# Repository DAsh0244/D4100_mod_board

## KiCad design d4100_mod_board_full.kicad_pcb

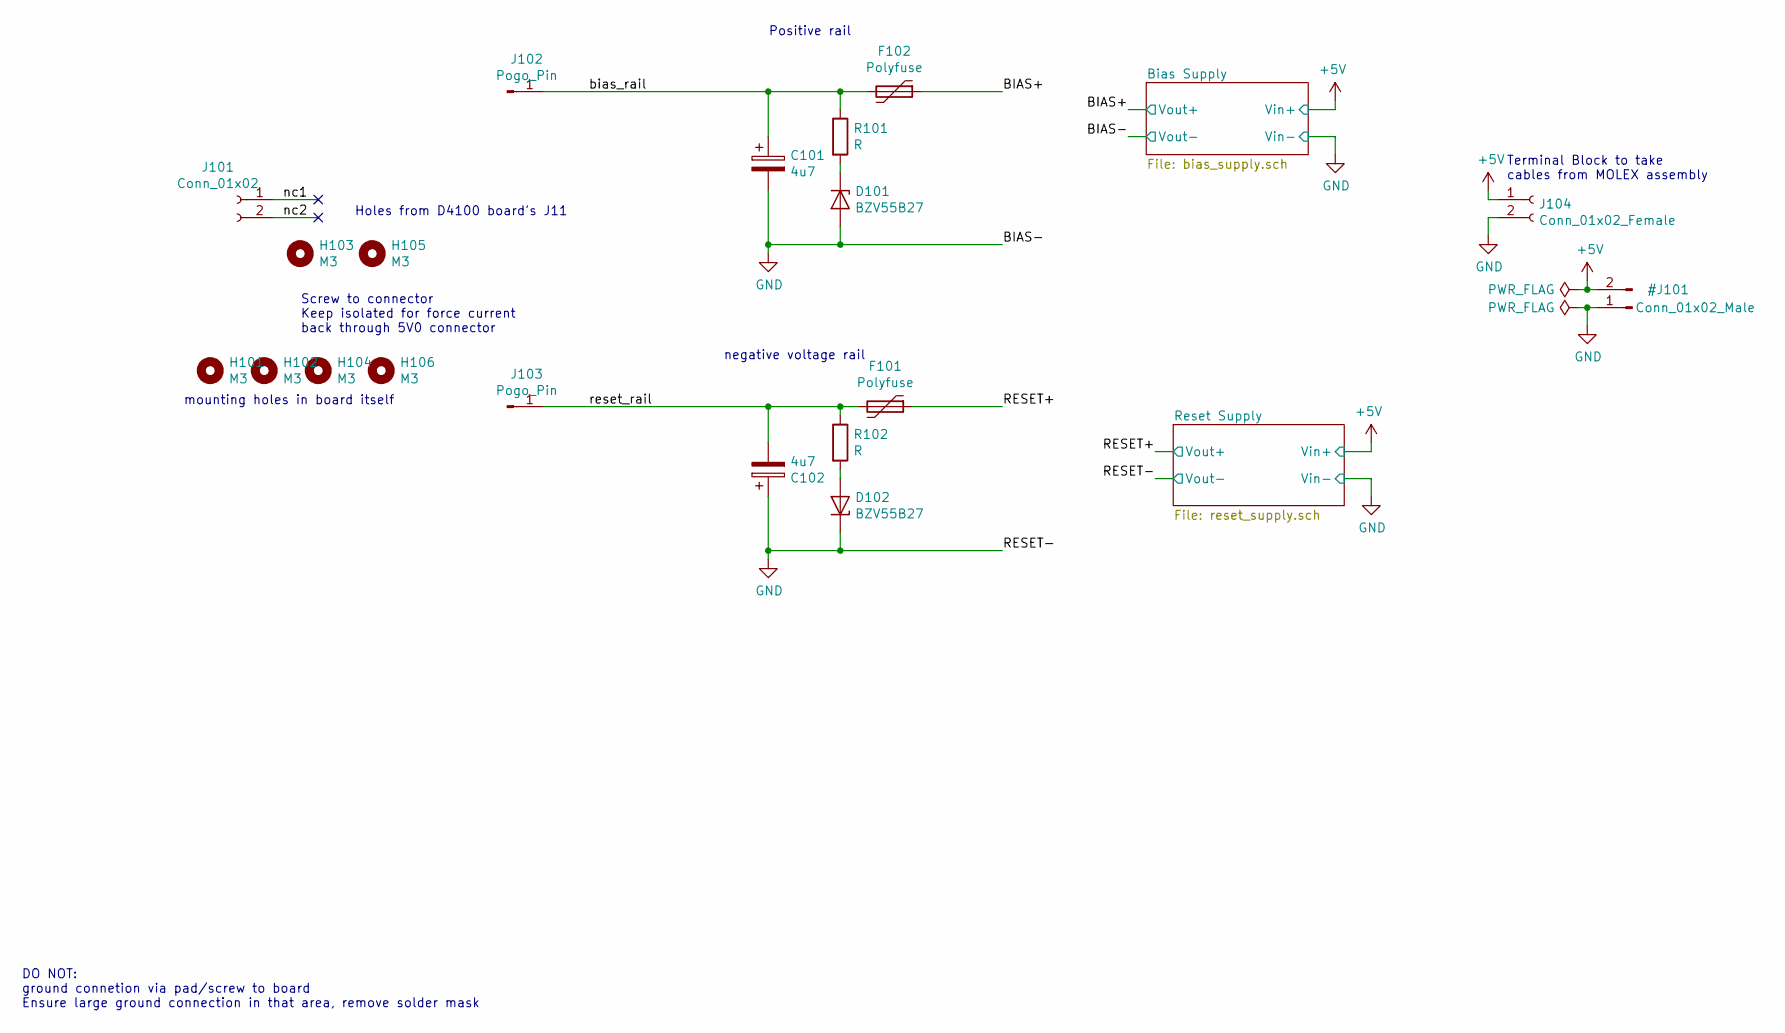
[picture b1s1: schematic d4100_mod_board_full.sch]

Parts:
C101, C102: 4u7; CP_Tantalum_Case-C_EIA-6032-28_Reflow
D101, D102: BZV55B27; D_MiniMELF
F101, F102: Polyfuse; Fuse_SMD1206_HandSoldering
H101, H102, H103, H104, H105, H106: M3; MountingHole_3.2mm_M3
J101: Conn_01x02; Pin_Header_Straight_1x02_Pitch2.54mm
J102, J103: Pogo_Pin; mill-max_0985-x-15-20-71-14-11-0
J104: Conn_01x02_Female; Phoenix_BCH-508HS-2
R101, R102: R; R_0805_HandSoldering

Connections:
/BIAS+: F102.1; also elsewhere on the board
/RESET+: F101.1; also elsewhere on the board
/bias_rail: C101.1, F102.2, J102.1, R101.1
/nc1: J101.1
/nc2: J101.2
/reset_rail: C102.2, F101.2, J103.1, R102.1
unnamed: D101.1 (K), R101.2
unnamed: D102.2 (A), R102.2

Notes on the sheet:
negative voltage rail
Positive rail
DO NOT: ground connetion via pad/screw to board Ensure large ground connection in that area, remove solder mask
Screw to connector Keep isolated for force current back through 5V0 connector
Terminal Block to take cables from MOLEX assembly
Holes from D4100 board's J11
mounting holes in board itself

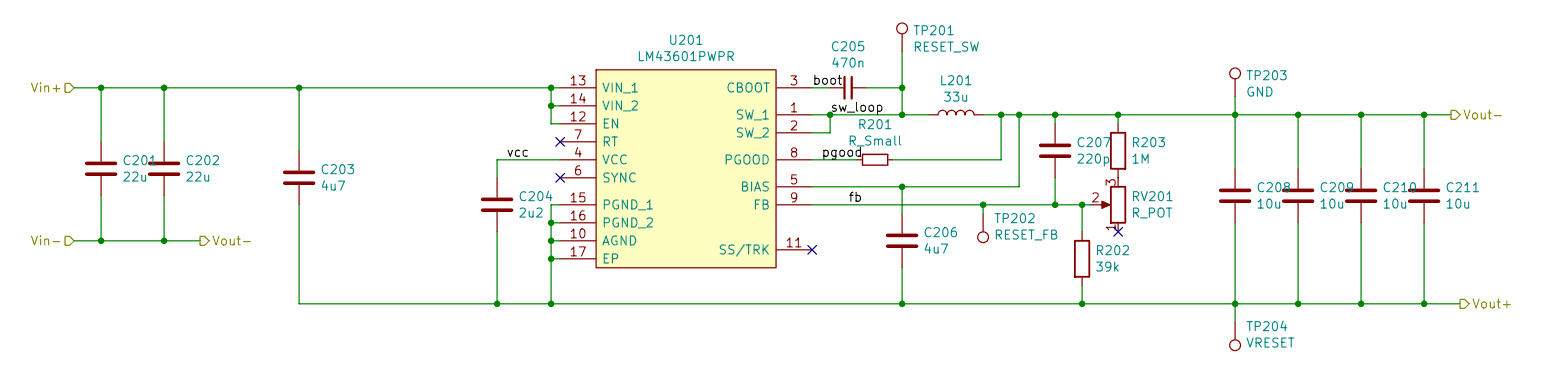
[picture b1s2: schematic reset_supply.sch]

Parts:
C201, C202: 22u; C_1210_HandSoldering
C203, C206: 4u7; C_0805_HandSoldering
C204: 2u2; C_0805_HandSoldering
C205: 470n; C_0805_HandSoldering
C207: 220p; C_0805_HandSoldering
C208, C209, C210, C211: 10u; C_1210_HandSoldering
L201: 33u; SRN4012TA
R201: R_Small; R_0805_HandSoldering
R202: 39k; R_0805_HandSoldering
R203: 1M; R_0805_HandSoldering
RV201: R_POT; PVG5A502C03R00
TP201: RESET_SW; Measurement_Point_Round-TH_Small
TP202: RESET_FB; Measurement_Point_Round-TH_Small
TP203: GND; Measurement_Point_Square-TH_Small
TP204: VRESET; Measurement_Point_Round-TH_Small
U201: LM43601PWPR; SOP65P640X120-17N; Manufacturer_Part_Number LM43601PWPR; Mouser Part Number 595-LM43601PWPR

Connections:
/RESET+: C203.2, C204.2, C206.2, C208.2, C209.2, C210.2, C211.2, R202.2, TP204.1, U201.10 (AGND), U201.15 (PGND_1), U201.16 (PGND_2), U201.17 (EP); also elsewhere on the board
/Reset Supply/boot: C205.2, U201.3 (CBOOT)
/Reset Supply/fb: C207.2, R202.1, RV201.2, TP202.1, U201.9 (FB)
/Reset Supply/pgood: R201.2, U201.8 (PGOOD)
/Reset Supply/sw_loop: C205.1, L201.1, TP201.1, U201.1 (SW_1), U201.2 (SW_2)
/Reset Supply/vcc: C204.1, U201.4 (VCC)
unnamed: R203.2, RV201.3

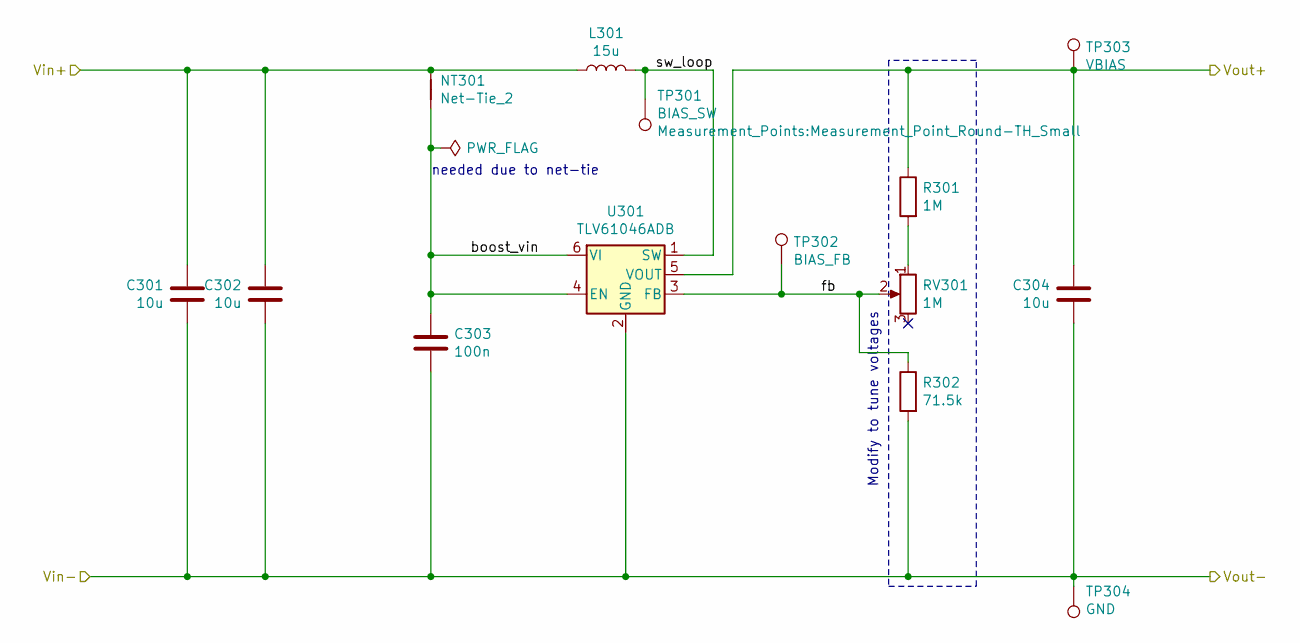
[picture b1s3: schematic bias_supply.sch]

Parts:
C301, C302, C304: 10u; C_1210_HandSoldering
C303: 100n; C_0805_HandSoldering
L301: 15u; WE-TPC_282892
NT301: Net-Tie_2; NetTie-I_SMD
R301: 1M; R_0805_HandSoldering
R302: 71.5k; R_0805_HandSoldering
RV301: 1M; PVG5A502C03R00
TP301: BIAS_SW; Measurement_Point_Round-TH_Small
TP302: BIAS_FB; Measurement_Point_Round-TH_Small
TP303: VBIAS; Measurement_Point_Round-TH_Small
TP304: GND; Measurement_Point_Square-TH_Small
U301: TLV61046ADB; SOT-23-6_Handsoldering

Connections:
/BIAS+: C304.1, R301.1, TP303.1, U301.5 (VOUT); also elsewhere on the board
/Bias Supply/boost_vin: C303.1, NT301.2, U301.4 (EN), U301.6 (VI)
/Bias Supply/fb: R302.1, RV301.2, TP302.1, U301.3 (FB)
/Bias Supply/sw_loop: L301.2, TP301.1, U301.1 (SW)
unnamed: R301.2, RV301.1

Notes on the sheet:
Modify to tune voltages
needed due to net-tie

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
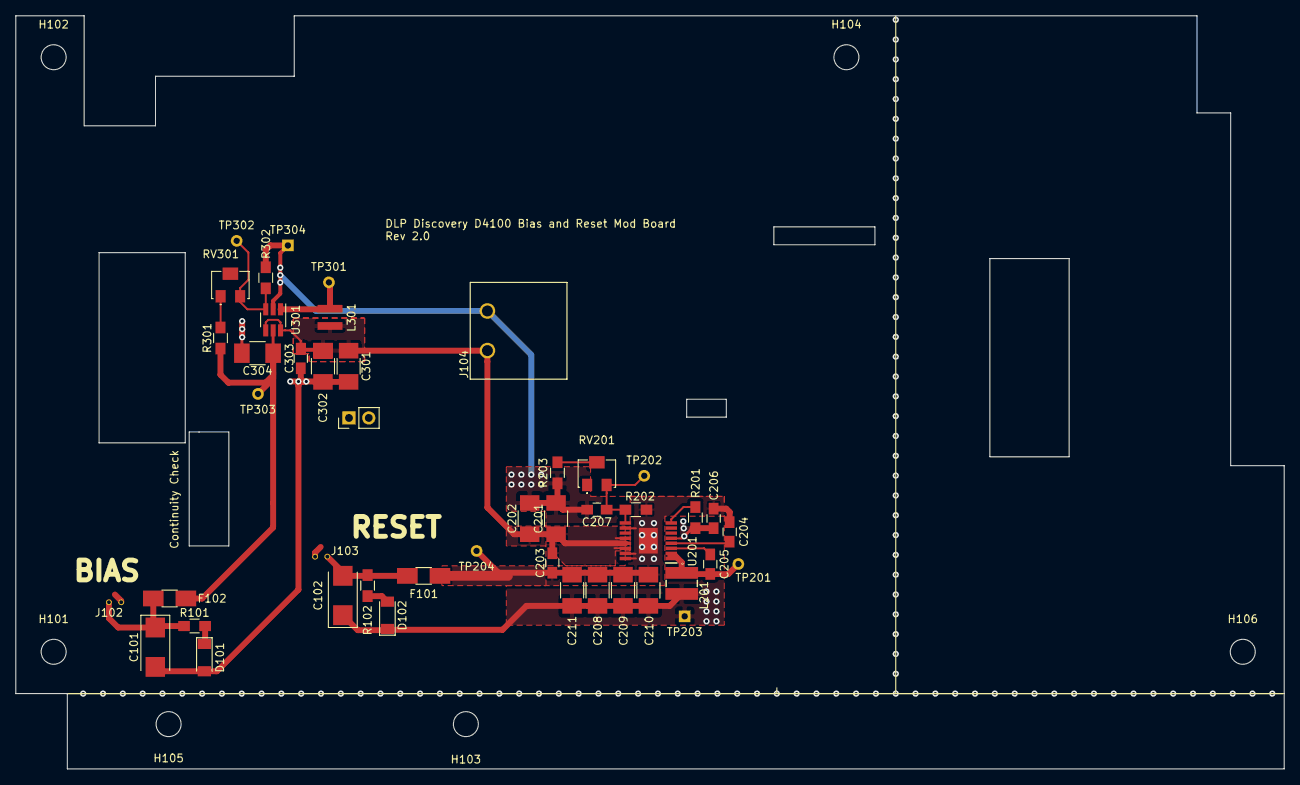
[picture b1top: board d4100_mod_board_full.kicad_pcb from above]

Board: 2 copper layers, 162.6 x 96.5 mm, 55 parts (0 on the bottom side), 18 nets.

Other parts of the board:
J102a, J103a: Pogo_Pin; mill-max_0985-x-15-20-71-14-11-0

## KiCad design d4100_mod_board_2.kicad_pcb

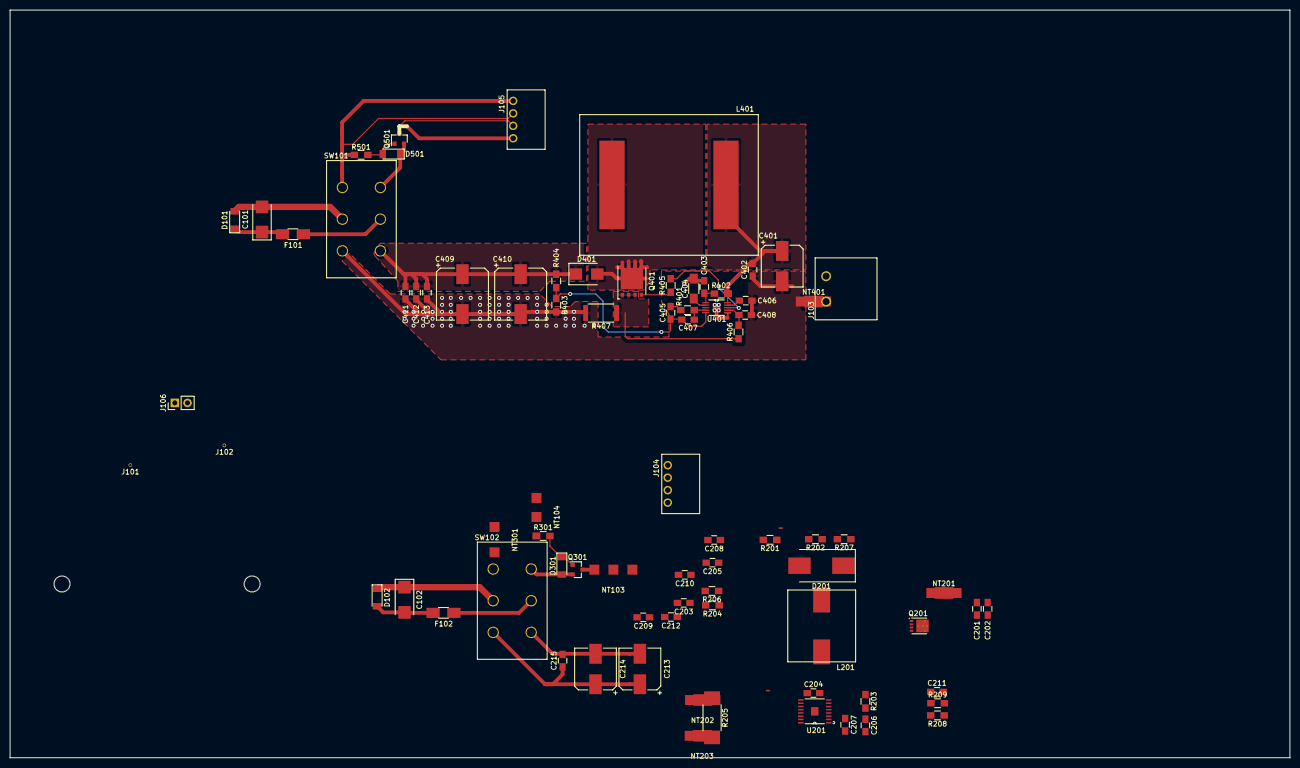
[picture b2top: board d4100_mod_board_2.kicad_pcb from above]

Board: 2 copper layers, 256.5 x 149.9 mm, 88 parts (0 on the bottom side), 59 nets.

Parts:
C101, C102: 4u7; CP_Tantalum_Case-C_EIA-6032-28_Reflow
C201: 10u; C_0805_HandSoldering
C202, C402: 470n; C_0805_HandSoldering
C203: 68n; C_0805_HandSoldering
C204: 22n; C_0805_HandSoldering
C205, C207, C208: 100n; C_0805_HandSoldering
C206: 300p; C_0805_HandSoldering
C209: 110p; C_0805_HandSoldering
C210: 510p; C_0805_HandSoldering
C211, C212, C408: 330p; C_0805_HandSoldering
C213, C214: 18u; CP_Elec_8x6.7
C215: 2u2; C_0805_HandSoldering
C401: 100u; CP_Elec_8x10
C403: 91p; C_0805_HandSoldering
C404: 39n; C_1206_HandSoldering
C405: 15n; C_0805_HandSoldering
C406, C411, C412, C413: 1u; C_0805_HandSoldering
C407: 680p; C_0805_HandSoldering
C409, C410: 68u; CP_Elec_10x10.5
D101, D102: BZV55B27; D_MiniMELF
D201: B560C-13-F; D_SMC_Handsoldering
D301, D501: ZMM5234B; D_MiniMELF
D401: MBRS2040LT3G; D_SMB
F101, F102: Polyfuse; Fuse_SMD1206_HandSoldering
H101, H102: M3; MountingHole_3.2mm_M3
J101, J102: Pogo_Pin; mill-max_0985-x-15-20-71-14-11-0
J103: Conn_01x02_Female; Phoenix_BCH-508HS-2
J104, J105: Conn_01x04_Female; Phoenix_PTSM_0,5_4-HH-2,5-THR
J106: Conn_01x02_Male; Pin_Header_Straight_1x02_Pitch2.54mm
L201: 3u7; L_Coilcraft_MLC1565
L401: 12u; PM2110-xxxx-RC
NT101, NT102, NT103, NT104: Net-Tie_3; NetTie-II_SMD
NT201, NT202, NT203, NT401: Net-Tie_2; NetTie-I_Connected_SMD
NT204, NT205: Net-Tie_2; NET-TIE-0.3mm
NT301, NT402, NT403, NT501: Net-Tie_2; NetTie-I_SMD
Q201: CSD18543Q3A; SON65P300X315X90-9N
Q301: DMN6140LQ-7; SOT-23
Q401: CSD18504Q5A; TDSON-8-1
Q501: DMP6350S-7; SOT-23
R201: 10k; R_0805_HandSoldering
R202: 3k57; R_0805_HandSoldering
R203: 41k2; R_0805_HandSoldering
R204: 18k7; R_0805_HandSoldering
R205: 6m; R_2512_HandSoldering
R206: 27k7; R_0805_HandSoldering
R207: 7k87; R_0805_HandSoldering
R208: 35k7; R_0805_HandSoldering
R209: 1k65; R_0805_HandSoldering
R301, R501: R; R_0805_HandSoldering
R401: 23k7; R_0805_HandSoldering
R402: 604k; R_0805_HandSoldering
R403: 560; R_0805_HandSoldering
R404: 57k6; R_0805_HandSoldering
R405: 13R7; R_0805_HandSoldering
R406: 1k05; R_0805_HandSoldering
R407: 6m; R_2512
SW101, SW102: SW_DPDT_x2; S202031MS02Q
U201: LM25088MH-1; SOP65P640X110-17N
U401: TPS40211DGQR; SOP50P490X110-11N

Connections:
+5V: C201.1, C202.1, C212.1, C401.1, C402.1, J103.2, L401.1, NT205.2, NT403.2, Q201.59
/BIAS+: C409.1, C410.1, C411.1, C412.1, C413.1, D401.1, R404.1, SW101.6
/BIAS-: C401.2, C402.2, C403.1, C404.2, C406.2, C408.2, C409.2, C410.2, C411.2, C412.2, C413.2, NT401.2, NT402.1, R403.2, R407.2, SW101.3, U401.11
/Bias Clamp/Vin+: NT101.1, Q501.3
/Bias Clamp/Vin-: NT102.1, NT501.2, R501.2
/Bias Supply/bp: C406.1, U401.9
/Bias Supply/comp: C407.1, R401.1, U401.4
/Bias Supply/fb: C405.2, C407.2, R403.1, R404.2, U401.5
/Bias Supply/gate: Q401.4, R405.2
/Bias Supply/gate_drive: R405.1, U401.8
/Bias Supply/rc: C403.2, R402.2, U401.1
/Bias Supply/sense: C408.1, R406.1, U401.7
/Bias Supply/shunt+: Q401.1, Q401.2, Q401.3, R406.2, R407.1
/Bias Supply/ss: C404.1, U401.2
/Bias Supply/sw_loop: D401.2, L401.2, Q401.5
/Bias Supply/vin: NT403.1, R402.1, U401.10
/PSU1+: J105.1, NT101.3
/PSU1-: J105.4, NT102.3
/PSU1_CLAMPED+: D501.1, Q501.2, SW101.4
/PSU1_CLAMPED-: NT501.1, SW101.1
/PSU2+: J104.4, NT104.3
/PSU2-: J104.1, NT103.3
/PSU2_CLAMPED+: D301.2, Q301.2, SW102.4
/PSU2_CLAMPED-: NT301.1, SW102.1
/PSU_SENSE1+: J105.2, NT101.2
/PSU_SENSE1-: J105.3, NT102.2
/PSU_SENSE2+: J104.3, NT104.2
/PSU_SENSE2-: J104.2, NT103.2
/RESET+: C203.2, C204.2, C205.2, C206.2, C207.2, C212.2, C213.2, C214.2, C215.2, NT203.2, R202.2, R204.2, R205.2, R209.2, SW102.6, U201.6, U201.17
/RESET-: C213.1, C214.1, C215.1, L201.2, NT201.2, NT204.1, R207.1, R208.1, SW102.3
/Reset Clamp/Vin+: NT103.1, Q301.3
/Reset Clamp/Vin-: NT104.1, NT301.2, R301.2
/Reset Supply/bootstrap: C208.2, U201.15
/Reset Supply/comp: C209.2, R206.2, U201.7
/Reset Supply/dither: C204.1, U201.10
/Reset Supply/enable: C203.1, R201.2, R202.1, U201.2
/Reset Supply/fb: C209.1, C210.1, C211.1, R208.2, R209.1, U201.8
/Reset Supply/gate_drive: Q201.4, U201.14
/Reset Supply/out_sense: NT204.2, U201.9
/Reset Supply/ramp: C206.1, R203.2, U201.4
/Reset Supply/rt: R204.1, U201.5
/Reset Supply/sense+: NT202.1, U201.12
/Reset Supply/sense-: NT203.1, U201.11
/Reset Supply/shunt+: D201.2, NT202.2, R205.1
/Reset Supply/ss: C207.1, U201.3
/Reset Supply/sw_loop: C208.1, D201.1, L201.1, Q201.1, Q201.2, Q201.3, U201.13
/Reset Supply/vcc: C205.1, R203.1, U201.16
/Reset Supply/vin: NT205.1, R201.1, U201.1
/bias_in: F101.1, SW101.5
/bias_rail: C101.1, D101.1, F101.2, J101.1
/reset_in: F102.1, SW102.5
/reset_rail: C102.2, D102.2, F102.2, J102.1
GND: C101.2, C102.1, C201.2, C202.2, D101.2, D102.1, J103.1, NT201.1, NT401.1, SW101.2, SW102.2
unnamed: C210.2, R206.1
unnamed: C211.2, R207.2
unnamed: C405.1, R401.2
unnamed: D301.1, Q301.1, R301.1
unnamed: D501.2, Q501.1, R501.1
unnamed: NT402.2, U401.6

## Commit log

2019-07-28 95% done
2019-07-29 spun up integrated version
